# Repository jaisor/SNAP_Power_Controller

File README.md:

# SNAP Power Controller

A small solar charger board for a single-cell (1S) Li-ion/LiPo battery, built for solar-powered LoRa mesh nodes such as [SNAP v1.2](https://makerworld.com/en/models/3360988-snap-v1-2-solar-node-adaptable-platform-2x200ma). Up to four 5V panels feed a CN3163 linear charger through a 5V input limiter. A switched output powers the node, and an INA3221 reports the battery's and the panels' voltage and current over I2C.

Designed in KiCad 10.

> **Branch `cn3163`:** this is a variant of the board on `main`. A CN3163 linear solar charger replaces `main`'s CN3791 buck charger. The board is the same size as `main`'s, with the same connectors in the same places.
>
> What changes in the circuit:
>
> - **Removed:** the switching stage and its support parts: Q1, D2, L1, the sense resistor R5, the MPPT divider R3/R4, C2, C4, C5 and the old R2. Ten parts go, one comes back (the new R2).
> - **Added:** R2 = 1.5k, which sets the charge current to 0.79A (1188V / R2). Also U3, an LDL1117S50R 5V regulator with its output capacitor C2, as an input voltage limiter.
> - **Kept:** the four diode-isolated solar inputs, the INA3221 and its two shunts, both switch headers, the reverse-battery FET, the status LEDs behind JP1, and every connector and pinout.
> - **Panel voltage:** every CN3163 pin has a 6.5V absolute maximum, and a panel floats to its open-circuit voltage once the battery is full. U3 sits between the panels and the charger and holds the charger's supply at 5.0V, so panels up to 18V open-circuit are safe. While charging, the CN3163 pulls the panels down to about 4.5V and U3 is simply fully on, costing about 0.3Ω: roughly 70mV at 0.25A and 0.25V at 0.8A. The board is still meant for 5–6V panels; anything higher only makes heat.
> - **Solar tracking is built in and fixed.** The CN3163 cuts the charge current to keep its input at 4.4V or above, so there is no set point to tune.
> - **It is a linear charger.** The difference between input and battery voltage is lost as heat in the chip, about 0.55W at 0.79A from panels, and up to about 1W when the supply holds 5V. It reduces the current by itself to stay near 130°C.

> **Status:** the schematic is complete and passes ERC. The PCB (36.4 × 23.6 mm, 1mm corner chamfers, four M2 mounting holes, two layers) is **placed and routed**, with no DRC errors and no schematic parity issues. It hasn't been built, and it hasn't had a manual layout review. The test results under [Testing](#testing) are from v1.0 boards with the CN3791 and an INA219.

## Built for solar mesh nodes

This controller is meant for solar mesh nodes like the [SNAP v1.2: Solar Node Adaptable Platform](https://makerworld.com/en/models/3360988-snap-v1-2-solar-node-adaptable-platform-2x200ma). It simplifies their build in three ways:

- **Easy, clean connections:** the panels, battery, node and switches each plug into their own connector.
- **Solar charging for 5V panels:** a charger that holds its input at 4.4V or above, so a weak panel isn't dragged down, with a diode for every panel built into the board.
- **I2C power sensing:** the battery and the total solar input, read at the same time.

I2C power sensors are supported natively by both [Meshtastic](https://meshtastic.org) and [MeshCore](https://github.com/meshcore-dev/MeshCore). In most cases the node recognizes the INA3221 automatically once it's connected.

In the SNAP v1.2 example build, shown below, the board replaces several separately wired parts:

| Example build part | With this board |
|---|---|
| CN3158 MPPT module (SDBK03TA) | CN3163 linear solar charger, holding its input at 4.4V or above and charging at 0.79A, behind a 5V input limiter |
| One 1N5819 per panel, soldered inline | A 1N5819W per input on the board, for up to four panels |
| Hand-soldered panel, battery and node wiring | Plug-in connectors for every connection: Micro JST 1.25, with 2.54mm pin headers for the switches |
| Latching on/off switch wired into the battery lead | Two switch connectors: SW_BATT cuts the battery, SW_LOAD cuts only the node |
| (none) | INA3221 power monitor on I2C, reading the battery and the total solar input at once |

### Example wiring

| Board connector | Connects to |
|---|---|
| J1, J2 (Solar_5V) | Two [FellDen 5V 200mA 110×60mm panels](https://www.amazon.com/dp/B0BND5NYGK), the ones SNAP v1.2 uses. J3 and J4 take up to two more |
| J5 (BATT) | An 18650 Li-ion cell (1S, 3.0–4.2V) in its holder |
| J8 (SW_LOAD) | The SNAP on/off switch cap's latching button. To cut the battery entirely, use J7 (SW_BATT) as well, or instead |
| J7 / J8 left unswitched | Both switch connectors are in series with the power path, so an unused one needs a 2.54mm jumper cap, or a wire bridging its pads on the back of the board. Otherwise the battery or the node stays disconnected |
| J6 (VOUT) | The XIAO nRF52840's BAT+ / BAT− pads, which is where SNAP powers it from the 18650 today |
| J9 (I2C) | XIAO 3V3 → VCC, D6 → SDA, D7 → SCL, GND → GND, on a 4-wire cable coloured red VCC, black GND, yellow SCL, white SDA. These pins need a Meshtastic build with I2C on D6/D7 (see the table below) |
| JP1 (LED) | Nothing. JP1 is bridged by a trace as supplied, so the status LEDs work. To turn them off for good, cut the trace between its pads |
| JP2 (NTC) | Nothing, or a 10k B3950 NTC taped to the cell. JP2 is bridged as supplied, which turns temperature sensing off. To use the NTC, cut the trace between JP2's pads and solder the NTC's wires to them |

The INA3221 reads the battery's charge and discharge current and what the panels deliver in total, both at the same time. There's no switch to set.

The XIAO's I2C pins depend on the firmware build. D4 and D5 can't be used with the Wio-SX1262, because the radio uses them.

| Firmware build | SDA | SCL | Status |
|---|---|---|---|
| Meshtastic `seeed_xiao_nrf52840_kit`, custom build with I2C on D6/D7 | D6 | D7 | Tested on a v1.0 board |
| Meshtastic `seeed_xiao_nrf52840_kit_i2c` | D6 | D7 | From the firmware source, not tested |
| Meshtastic `seeed_xiao_nrf52840_kit`, unmodified (D6/D7 are reserved for the GNSS module) | NFC1 pad (underside) | NFC2 pad (underside) | From the firmware source, not tested |
| MeshCore `Xiao_nrf52` | D7 | D6 | From the firmware source, not tested |

The INA3221 uses address 0x42. Meshtastic also expects the DFRobot Lark weather sensor at 0x42, so the two can't share a bus.

In Meshtastic, enable power metrics in the telemetry settings so the readings are sent to the mesh.

## Features

- **Solar input:** up to four 5V panels in parallel (Micro JST 1.25), each isolated by its own 1N5819W Schottky (SOD-123), good for 0.5A per input, so a shaded or unplugged panel doesn't drag the others down.
- **Input limiter:** U3, an LDL1117S50R 5.0V regulator (ST), keeps the charger's supply at or below 5V, so panels up to 18V open-circuit can't damage the 6.5V-rated charger. While charging it is fully on and only adds its on-resistance.
- **Charging:** [CN3163](https://kaspars.net/wp-content/uploads/2023/12/CN3163.pdf) linear charger for one cell. Charges at 0.79A to 4.2V (1%), CC/CV, with a 10% precharge for deeply discharged cells, termination at 10% of the charge current and automatic recharge. An on-chip loop reduces the charge current to keep its input at 4.4V or above, and thermal regulation reduces it to keep the chip near 130°C.
- **Battery and load switching:** connectors for two panel-mount switches. **SW_BATT** disconnects the battery from everything. **SW_LOAD** cuts only the output, so the battery keeps charging.
- **Output:** VOUT connector (Micro JST 1.25) that powers the module from the battery.
- **Reverse-battery protection:** Q2, a P-channel MOSFET between the battery connector and the rest of the board. A cell plugged in backwards is blocked instead of shorting through the charger. With the cell the right way round, Q2 is fully on in both directions, adding about 60mV of drop at 0.8A.
- **Power monitoring:** [INA3221](https://www.ti.com/lit/ds/symlink/ina3221.pdf) at I2C address 0x42, on two channels: the battery (bidirectional current plus voltage) and the total solar input. The third channel is unused.
- **Battery temperature (optional):** with a 10k B3950 NTC against the cell, wired to JP2's pads, the CN3163 pauses charging below about 1°C and above about 46°C. JP2 is bridged by a thin trace as supplied, which turns sensing off; cut the trace to use the NTC.
- **Status LEDs:** red while charging, green when charging is done. They're powered through JP1, marked `LED` on the top of the board: two pads joined by a trace, the same as JP2. As supplied the LEDs work, and a lit LED draws about 3mA from the panels (never from the cell). Cut the trace to disconnect them; a solder blob across the pads turns them back on.

## Choosing panels

While charging, the CN3163 holds its input at 4.4V or above. Each input diode drops about 0.35V and U3 another 0.07–0.25V, so a panel has to deliver its power at about 4.8–5.0V. A panel's maximum-power voltage falls about 0.4% per °C, so what matters is how the panel does hot, not at its rated 25°C.

- **"6V" panels** (12 cells, about 7.2V open-circuit) are preferred. They stay above that voltage in heat.
- **"5V" panels** (10 cells, about 6.0V open-circuit) lose part of their output on hot days, when their maximum-power voltage falls to about 4.2V.
- **"5V" panels that only reach about 5.5V open-circuit** lose most of their output in heat.

There is no setting to change for a different panel: the CN3163's 4.4V input threshold is fixed. `main`'s README models the CN3791 board, whose set point is about the same, for the two kinds of 5V panel; expect a little less here, because of U3's drop.

## Schematic

The schematic follows the CN3163 datasheet's typical application circuit (Figure 1), with these changes:

| Item | Value | Why |
|---|---|---|
| Charge current | 0.79A (R2 = 1.5k) | I<sub>CH</sub> = 1188V / R2. Leaves margin on the 1.0A-rated connectors; use 2.4k for 0.5A with small cells. |
| Input limiter U3 | LDL1117S50R, 5.0V, SOT-223 | Every CN3163 pin is rated 6.5V at most, and an unloaded panel sits at its open-circuit voltage. A shunt clamp would have to sink about half of each panel's short-circuit current to hold it down, and an overvoltage cut-off would switch off in bright sun, so a series regulator was used. U3 is rated for 18V in (20V absolute maximum). Its output capacitor C2 is 10µF. |
| Status LED supply | From U3's output | The LEDs' resistor R1 and JP1 take their supply after U3, because CHRG and DONE are 6.5V pins too. |
| Battery capacitor C3 | 10µF | The datasheet asks for 1µF to 22µF on BAT. |
| Temperature divider | R3 = 4.7k (VCHG to TEMP), R4 = 47k (TEMP to GND), NTC across R4 | The datasheet's Figure 7. Charging runs while TEMP is between 45% and 80% of the CN3163's supply, so the window doesn't depend on the panel voltage. Sized for a 10k B3950 NTC and 0–45°C, the exact values are 4.86k and 46.1k; 4.7k and 47k give about 1–46°C. |
| Temperature jumper JP2 | Bridged by a trace; its pads are the NTC's pads | Without an NTC, TEMP would sit at 91% and charging would never start. Bridged, JP2 holds TEMP at GND, which turns sensing off, as the datasheet allows. R3 then draws about 1mA from the 5V supply while the panels are lit. Cut the trace before fitting the NTC. |
| Blocking diode | none | The input diodes stop the battery feeding back into the panels. In the dark the CN3163 sleeps and draws under 3µA from the battery (datasheet figure, not measured on a board). |
| Input diodes | 1N5819W, SOD-123 (40V/1A) | Rated 0.5A per input here: about 0.2W in the diode, which the SOD-123 package handles with margin in a warm enclosure. |

## PCB

| Area | Parts |
|---|---|
| Corners | M2 mounting holes H1–H4 |
| Top edge | Solar inputs J1 (`+S1-`) and J2 (`+S2-`), the 4-pin I2C connector J9, then the INA3221 (U2) with its bypass capacitor C6 |
| Upper middle | Input diodes D5/D6, the solar shunt R7 and the input capacitor C1, with the I2C pull-ups R8/R9 above the charger and its current-setting resistor R2 beside them. On the right: the reverse-battery MOSFET Q2 and the battery shunt R6 |
| Middle | CN3163 (U1), with the 5V limiter U3 below and to its left. The limiter's output capacitor C2 is under U1, and the battery capacitor C3 to its right. The status LEDs D3/D4 and R1 sit beside the LED solder jumper JP1 at the left edge |
| Left edge, top | The NTC pads JP2 (`NTC`) left of D5, with the temperature divider R3/R4 below them |
| Right edge | Battery (J5, `+1S BATT-`) and VOUT (J6, `+LOAD-`) |
| Bottom edge | Solar inputs J4 (`+S4-`) and J3 (`+S3-`), directly under J1 and J2, with their diodes D8/D7, then the switch headers J7 (`SW BATT`) and J8 (`SW LOAD`) |

The connectors, the INA3221, the input diodes, the shunts, Q2 and the LEDs are in exactly the same places as on `main`'s board (JP1 sits 3.2mm lower and R1 lies flat under D3, to make room for R3/R4); only the charger parts in the middle differ. Reference designators aren't printed; the silkscreen carries only function labels. The holes are plain non-plated 2.2mm M2 holes, 2.5mm in from each edge. Mount the board with nylon washers and standoffs; see [Dimensions](#dimensions).

The CN3163's 3D model doesn't show in the renders (the footprint's model file seems to be missing from KiCad's library); only its pads appear.

### Dimensions

The [wiring diagram](#built-for-solar-mesh-nodes) includes a dimension drawing to scale.

| | |
|---|---|
| Outline | 36.4 × 23.6mm, with a 1mm × 45° chamfer on each corner |
| Thickness | 1.6mm PCB, two layers. All parts are on the top side; the through-hole connector pins stick out the back |
| Mounting holes | Four, 2.2mm diameter, not plated, for M2 screws |
| Mounting hardware | M2 screws with heads no wider than 4mm, and nylon washers and standoffs. **Don't use metal washers or metal standoffs:** a 5mm M2 washer reaches within 0.3mm of C6's bare pad at H2, and tracks pass about 3mm from the hole centres |
| Hole positions | One in each corner, centre 2.5mm from both edges |
| Hole spacing | 31.4mm across, 18.6mm down, centre to centre |

**Silkscreen labels:**

- **Connector labels with polarity:** each solar, battery and VOUT connector has one label centred under or over it, with `+` on the pin-1 side and `-` on the GND side: `+S1-` to `+S4-` on J1–J4, `+1S BATT-` on J5 and `+LOAD-` on J6.
- **Switch headers:** `SW BATT` (J7) and `SW LOAD` (J8) are vertical labels left of the headers.
- **I2C connector:** `I2C` under J9 on the front. The pin names (`VCC`, `GND`, `SCL`, `SDA`) are printed under its pads on the back.
- **LED jumper:** `LED` beside JP1.
- **NTC pads:** `NTC` above JP2.
- **Back:** the module ID, "SNAP Power Controller CN3163 v1.0 / Nov. 20, 2026". Under it, a reminder to check polarity, the limits listed under [Safety](#safety), and a short no-warranty notice.
- **Text size:** the front labels are 0.6mm text, the board's minimum. Board houses often recommend 0.8–1mm or more, so check that yours prints 0.6mm cleanly. The back label is 0.8 to 1.0mm.

**Routing** (a grid auto-router adapted from `tools/route-pcb.py`, with the tightest connections placed by hand first; the board file is the source of truth):

- **Ground:** both layers have a GND pour, and the bottom one is cut only by short hops. Most surface-mount GND pads have their own via to it. Six vias in the CN3163's exposed pad carry its heat to the bottom plane, and no track runs on the bottom layer under the chip.
- **Power path:** R7 → C1 → U3 → U1 → C3 → J7 runs on short tracks on the top layer.
- **Track widths:** power paths are 0.6mm, 0.4mm where 0.6mm doesn't fit. Signals are 0.25mm, with 0.2mm on the INA3221's escape tracks.
- **Kelvin sensing:** the INA3221's channel inputs connect straight to the pads of their shunt resistors (R6, R7).
- **Temperature line:** TEMP runs on the bottom layer from U1 pin 1 to the NTC pads, under the input diodes, so it is the one long track that cuts the bottom ground plane.
- **Layer use:** about 277mm of track on the top layer and 84mm on the bottom.
- **Size:** 199 track segments and 44 vias, 17 of them on GND. VCHG reaches the NTC divider (R3) on the bottom layer, under JP1.
- **Mounting holes:** no copper except ground comes within 3mm of a hole centre, apart from two bare pads: C6's at H2 (2.8mm) and JP1's at H3 (2.7mm, fed through R1, 1k). That's why the hardware must be nylon.
- **Checks:** DRC reports 0 violations and 0 unconnected items, and schematic parity is clean.

Review it before ordering, especially the charger's heat path (the exposed pad, its vias and the ground plane).

Still to do: a manual layout review before ordering (see Fabrication).

## Connectors

| Ref | Connector | Pin 1 | Pin 2 | Notes |
|---|---|---|---|---|
| J1–J4 | Micro JST 1.25, 2-pin | Panel + | GND | 5V solar panels, any combination of 1–4 |
| J5 | Micro JST 1.25, 2-pin | Battery + | GND | 1S Li-ion/LiPo, 4.2V |
| J6 | Micro JST 1.25, 2-pin | VOUT | GND | Battery voltage out to the powered module, through SW_LOAD |
| J7 | 2.54mm pin header, 2-pin | VBAT (charger) | BATT+ (battery) | SW_BATT: panel-mount SPST switch, rated ≥1A or the module's peak current |
| J8 | 2.54mm pin header, 2-pin | VBAT | VOUT | SW_LOAD: panel-mount SPST switch, same rating |
| J9 | Micro JST 1.25, 4-pin | VCC (3.3–5V) | GND | Pin 3 = SCL, pin 4 = SDA, matching the common red/black/yellow/white 4-wire cable. VCC comes from the MCU and powers the INA3221. v1.0 boards have SDA on pin 2 and GND on pin 4. |

J1–J6 and J9 are Micro JST 1.25 (Molex PicoBlade-compatible) vertical headers, Molex 53047-0210 (2-pin) and 53047-0410 (4-pin). They mate with standard female cable housings (Molex 51021). J7 and J8 are standard 2.54mm vertical pin headers, which take a 2.54mm female housing or a jumper cap. Notes:

- **Current:** PicoBlade contacts are rated 1.0A. The charge current is set to 0.79A to stay under that on the battery connector (J5). Keep the module's load current under 1A too, since it flows through J5 when the panels are dark.
- **No keying between functions:** J1–J6 are the same 2-pin type, so a battery lead fits a solar socket. Check the silkscreen before plugging in. The switch headers take a different plug, so they can't be mixed up with these.
- **Battery polarity:** "JST 1.25" LiPo pigtails have no standard polarity. Check that red goes to the pin marked `+` (pin 1 on J5) before connecting. Q2 blocks a reversed cell, but fit the cell with SW_BATT off anyway: with SW_BATT on in sunlight, the charger's output can partly turn Q2 on and push a limited current into a reversed cell, which heats Q2.
- **NTC:** JP2 is not a connector: its two pads take the NTC's wires directly. Either way round works. Keep the NTC on the cell, away from the board: the CN3163 itself runs hot.
- **Reading the marks:** each of J1–J6 has a `+name-` label: pin 1 (`+`) is on the `+` side and GND on the `-` side. All six face the same way, so pin 1 is the left pin with the board read as printed.

**Operating note:** if SW_BATT is off while the panels are in sun, the charger has no battery to charge, and its output isn't meant to power the node in that state. Keep SW_LOAD off then.

## Power monitor (INA3221)

- **Address:** 0x42 (A0 = SDA). That's the INA3221 default in both Meshtastic and MeshCore.
- **Shunts:** both are 0.1Ω, which both firmwares assume. Full scale is ±163.8mV, so about ±1.64A, in 0.4mA steps.
- **What it can't measure:** sleep current. A sleeping node draws 50–100µA, which is 5–10µV across 0.1Ω, below the chip's 40µV step and its offset (up to 80µV). The monitor is for charge and load telemetry, in the tens to hundreds of milliamps; profile sleep current on the bench with a tool made for it. A larger battery shunt isn't an option here: 0.5–1Ω would drop 0.4–0.8V at the 0.79A charge current and exceed the chip's input range.
- **Pull-ups:** R8/R9 are 10k I2C pull-ups to the MCU's VCC. Leave them off if the MCU board already has pull-ups.

| Channel | Shunt | Current | Bus voltage |
|---|---|---|---|
| 1 | R6, between BATT+ and the cell | Positive while charging, negative while discharging | Cell voltage, readable even with SW_BATT off. It's measured after Q2, so it reads up to about 50mV off while current flows |
| 2 | R7, between the PV bus and VIN | Total solar current, always ≥ 0 | VIN (panel voltage minus the diode drop), before the 5V limiter |
| 3 | None: both inputs are tied to GND | Unused, reads zero | Unused, reads zero |

**Firmware support** (checked in the source code on 2026-11-09, not yet on hardware):
- **Meshtastic:** looks for an INA3221 at 0x42. It reports all three channels' voltage and current as power metrics (channel 3 reads about zero on this board), and uses channel 1 as the battery by default.
- **MeshCore:** the XIAO nRF52 build includes INA3221 support (`ENV_INCLUDE_INA3221`). It reports voltage, current and power for each channel.

## Testing

The CN3163 board hasn't been built. These tests are from v1.0 boards, which have the CN3791 charger and an INA219:

| Test | Setup | Status |
|---|---|---|
| First power-up | Board wired to a XIAO + Wio-SX1262, running Meshtastic built from `seeed_xiao_nrf52840_kit` with I2C on D6/D7 | Done. Everything seems to work as expected, including the INA219 over I2C |
| INA219 battery current | Same setup, battery at about 4V | Done. Discharging: about −12 to −15mA. Charging from the XIAO's USB: +100mA |
| Sunlight | Board wired into a real solar node with 4 × 60mA panels, with metrics tracked in Grafana dashboards | In progress. Voltage and charge current rose as expected when exposed to sunlight. One reading in the Meshtastic app: 4.56V, 110.5mA |

The signs match the expected convention: positive while charging, negative while discharging. The USB reading comes from the XIAO's own charger, so it doesn't test the board's charger. The sunlight reading is from SW3's SOLAR position: 4.56V is above a Li-ion cell's 4.2V and close to the 4.58V MPPT set point of the board tested. It's a single reading, and longer-term results are still to come. These tests used a board with Micro JST 1.25 connectors on J7 and J8, so the pin-header version hasn't been built yet. In the sunlight test build, J7 and J8 are bridged with wire on the back of the board, so neither switch is fitted.

## Safety

This is an experimental design for charging a lithium-ion cell. It's provided as is, with no warranty, and hasn't been certified to any safety standard. If you build it, you're responsible for:

- Assembling it correctly and checking connector polarity before connecting a cell. J1–J6 share one connector type, so a lead plugs into the wrong socket easily. Q2 protects against a reversed cell on J5, but not against every fault, such as a battery plugged into a solar input.
- Using a protected cell or a separate protection circuit. The CN3163 charges the cell but doesn't protect it from over-discharge or short circuits.
- Deciding on temperature sensing. As supplied, JP2 turns it off, and the board will charge a frozen or hot cell. Li-ion cells shouldn't be charged below 0°C; fit the NTC if the node sees frost or strong sun.
- Allowing for heat. The CN3163 is a linear charger and turns up to about 1W into heat at full current; it limits itself near 130°C, but the board and the enclosure around it get warm.
- Fusing, wiring and an enclosure suited to where the node is installed, including outdoor heat and moisture.
- Mounting it with nylon washers and standoffs. Metal hardware can reach copper near the holes, including the unfused battery rail.
- Not using it where a failure could hurt someone or damage property.

**Limits**, also printed on the back of the board:

| | Limit | Set by |
|---|---|---|
| Battery | One Li-ion or LiPo cell (1S), charged to 4.2V | The CN3163's fixed charge voltage |
| Panel voltage | 18V open-circuit at most. The board is meant for 5–6V panels; a higher-voltage panel is safe but its extra voltage is only lost as heat | The input rating of U3, the 5V limiter in front of the charger |
| Panel current | 0.5A per input | Heat in each input's 1N5819W diode |
| Load on VOUT | 1A | The connector contacts at J5 and J6 |

**No warranty:** the board is provided as is, and you use it at your own risk. Where the law allows a limit, liability for a board you bought is limited to the price you paid for it. The design itself is covered by the disclaimer in the [licence](#license).

## Fabrication

This board's release is [v1.0_cn3163](https://github.com/jaisor/SNAP_Power_Controller/releases/tag/v1.0_cn3163) (Nov. 20, 2026), with the files below attached. The repository's latest release, v1.1, is `main`'s CN3791 board, and its files don't match this one. The commands below regenerate the package into `output/fab/`, which isn't tracked in git:

| File | Contents |
|---|---|
| `SNAP_Power_Controller_CN3163_v1.0_gerbers.zip` | Upload this to the board house. 9 Gerber X2 layers (copper, mask, paste and silkscreen on both sides, plus the outline), a Gerber job file, plated and non-plated Excellon drill files, and drill maps |
| `FAB_NOTES.txt` | Order settings: 2 layers, FR-4 1.6mm, 1oz copper, 36.4 × 23.6mm, 0.2mm/0.2mm minimum track/space, 0.3mm minimum drill, tented vias, four 2.2mm non-plated holes. Also assembly cautions |
| `SNAP_Power_Controller_CN3163_v1.0_BOM.csv` | BOM in JLCPCB format (Comment, Designator, Footprint, LCSC Part #), plus a Manufacturer Part column for the specific parts |
| `SNAP_Power_Controller_CN3163_v1.0_CPL.csv` | Pick-and-place file for top-side assembly, in the same coordinates as the Gerbers |

Every BOM line has a JLCPCB/LCSC part number, checked on jlcpcb.com on Nov. 20, 2026. They are Basic parts except D3, the connectors, U1, U2 and U3. Re-check stock before ordering, and check rotation and polarity in the assembler's preview. D5–D8 are Changjiang B5819W (C8598), rated 1A with 0.6V at most at 1A. The PicoBlade headers and the J7 and J8 pin headers are through-hole parts. JP1 is a solder jumper made of bare pads, so it has no part to place.

Regenerating the package (after the board is final and DRC is clean):

```bash
OUT=output/fab
P=SNAP_Power_Controller
kicad-cli pcb export gerbers --layers F.Cu,B.Cu,F.Paste,B.Paste,F.Silkscreen,B.Silkscreen,F.Mask,B.Mask,Edge.Cuts --subtract-soldermask --check-zones -o $OUT/gerbers $P.kicad_pcb
kicad-cli pcb export drill --format excellon --excellon-units mm --excellon-zeros-format decimal --drill-origin absolute --excellon-separate-th --generate-map --map-format gerberx2 -o $OUT/gerbers/ $P.kicad_pcb
kicad-cli pcb export pos --format csv --units mm --side both -o $OUT/pos-kicad.csv $P.kicad_pcb
kicad-cli sch export bom --fields 'Value,Reference,Footprint,${QUANTITY}' --labels 'Comment,Designator,Footprint,Qty' --group-by 'Value,Footprint' --ref-range-delimiter '' --exclude-dnp -o $OUT/bom-kicad.csv $P.kicad_sch
node tools/fab-package.js $OUT
```

## Repository layout

```
SNAP_Power_Controller.kicad_pro / .kicad_sch / .kicad_pcb   KiCad project
SolarNode.kicad_sym             project symbol library (CN3163)
SolarNode.pretty/               project footprint library (JP2's bridged NTC pads)
sym-lib-table / fp-lib-table
tools/
  gen-schematic.js              generates the schematic (Node)
  place-pcb.py                  places the earlier 52 × 29mm CN3163 board: footprints, labels, holes, outline (KiCad Python / pcbnew)
  draw-routes.py                draws the earlier 52 × 29mm board's tracks, vias and GND pours (run after place-pcb.py)
  route-pcb.py                  the earlier auto-router, kept for reference (v1.0's copper came from it)
  make-diagram.py               draws docs/images/wiring-diagram.png from the board render
  fab-package.js                JLCPCB-style BOM/CPL, fab notes and Gerber zip from the kicad-cli exports
docs/images/                    images used in this README (snap/: photos from the SNAP v1.2 MakerWorld post)
CLAUDE.md                       design decisions and working notes
LICENSE                         CERN-OHL-P-2.0 (hardware design and documentation)
tools/LICENSE                   MIT (scripts)
```

The schematic is generated by `tools/gen-schematic.js`. The board was built from it and routed with a router that isn't in the repo, so the board file is the source of truth for the layout; the board scripts in `tools/` build the earlier 52 × 29mm layout. Both are checked with `kicad-cli` ERC/DRC (including schematic parity). See [CLAUDE.md](CLAUDE.md) for the full design rationale and workflow. Generated outputs (`output/`: BOM, reports, fab files) are not tracked.

## Regenerating the design

The schematic can be rebuilt from its script. Run these from the repo root, with `kicad-cli` from KiCad 10:

```bash
# Schematic (Node): rewrites the .kicad_sch, SolarNode.kicad_sym and sym-lib-table
node tools/gen-schematic.js
kicad-cli sch erc --format json --severity-all -o erc.json SNAP_Power_Controller.kicad_sch
# Board check: expect 0 violations, 0 unconnected, 0 parity issues
kicad-cli pcb drc --schematic-parity --severity-all --format json -o drc.json SNAP_Power_Controller.kicad_pcb
```

**Don't run `tools/place-pcb.py` or `tools/draw-routes.py` on this design.** They rebuild the earlier 52 × 29mm board and overwrite the board file. The scripts overwrite their output files. Once you edit the schematic in KiCad, stop regenerating it (or port your edits into the script first).

Refreshing the images in `docs/images/`:

```bash
kicad-cli sch export svg -o docs/images SNAP_Power_Controller.kicad_sch
kicad-cli pcb render --side top --width 1600 --height 900 --quality high --zoom 1.35 -o docs/images/pcb-top.png SNAP_Power_Controller.kicad_pcb
kicad-cli pcb render --side bottom --width 1600 --height 900 --quality high --zoom 1.35 -o docs/images/pcb-bottom.png SNAP_Power_Controller.kicad_pcb
kicad-cli pcb render --width 1600 --height 1000 --quality high --perspective --rotate "-40,0,-25" -o docs/images/pcb-iso.png SNAP_Power_Controller.kicad_pcb
```

(The schematic export is named `SNAP_Power_Controller.svg`; rename it to `schematic.svg`.)

After refreshing `pcb-top.png`, redraw the wiring diagram with KiCad's Python, which includes Pillow and NumPy:

```bash
"C:/Program Files/KiCad/10.0/bin/python.exe" tools/make-diagram.py
```

## License

Copyright 2026 Jordan Marinov (JaisorGadgets).

The hardware design (schematic, board, symbol library) and its documentation, including the images in `docs/images/`, are licensed under the [CERN Open Hardware Licence Version 2 – Permissive](LICENSE) (CERN-OHL-P-2.0). You may redistribute and modify them, and make and sell products from them, under the terms of the licence. They are distributed WITHOUT ANY EXPRESS OR IMPLIED WARRANTY, INCLUDING OF MERCHANTABILITY, SATISFACTORY QUALITY AND FITNESS FOR A PARTICULAR PURPOSE. See section 5 of the licence for the disclaimer and limitation of liability.

The scripts in `tools/` are licensed under the [MIT License](tools/LICENSE).

Source location: https://github.com/jaisor/SNAP_Power_Controller

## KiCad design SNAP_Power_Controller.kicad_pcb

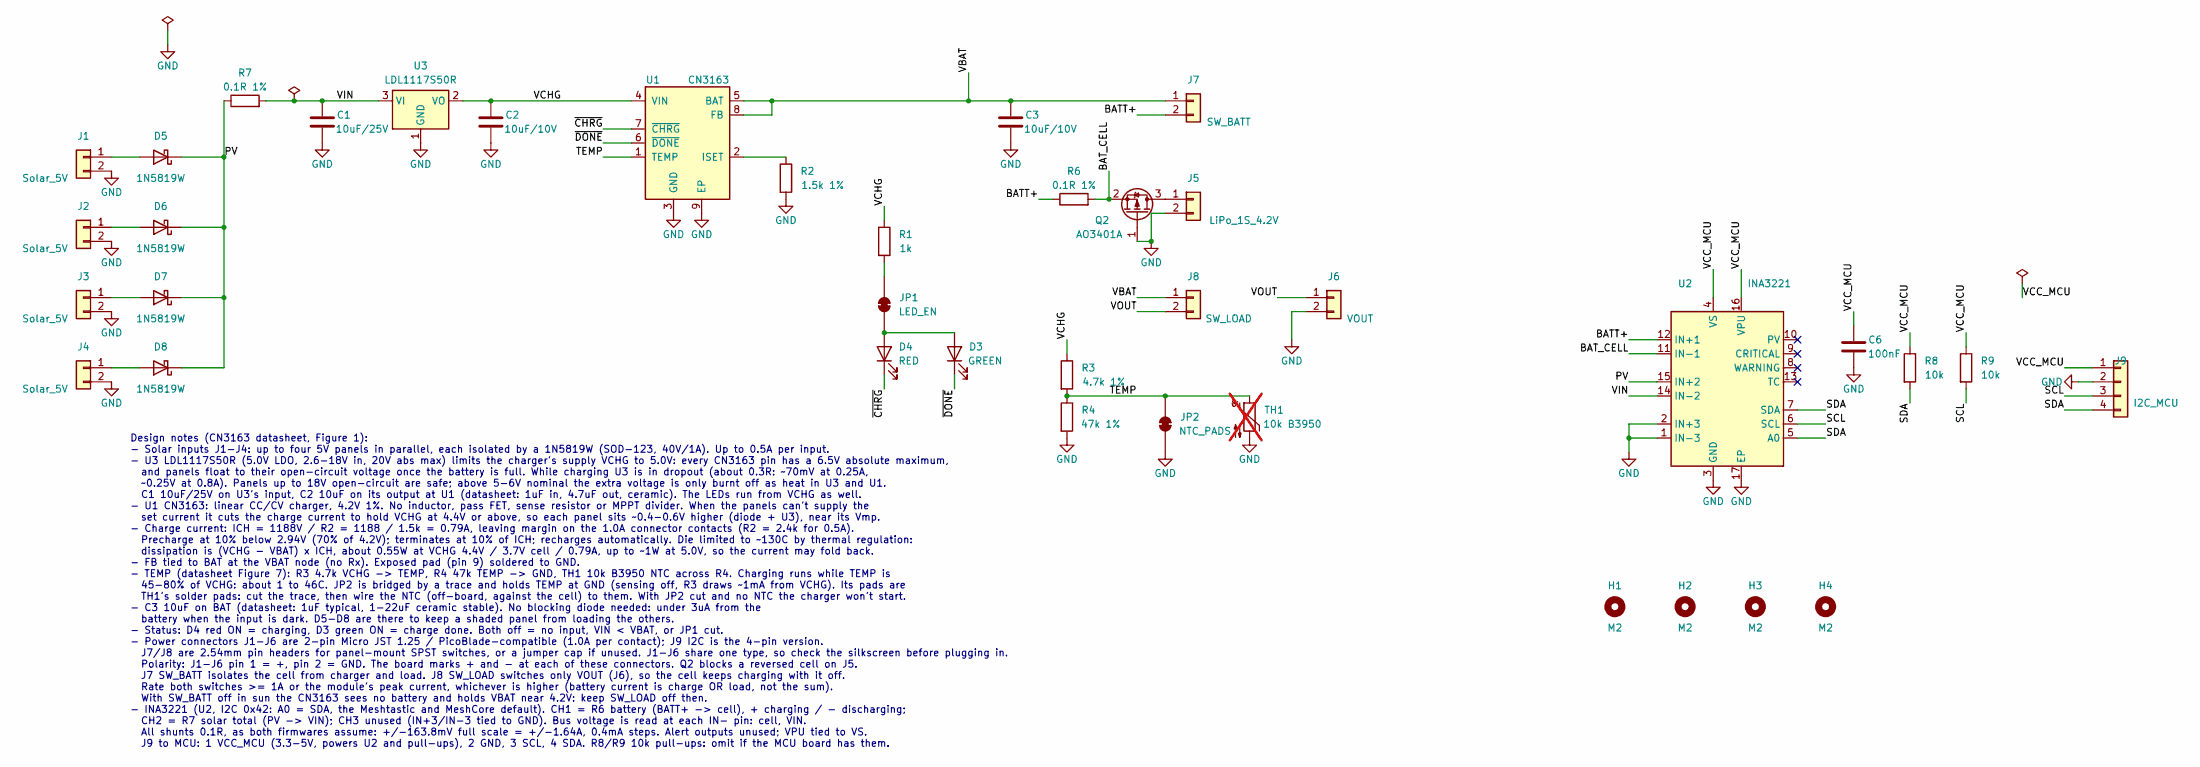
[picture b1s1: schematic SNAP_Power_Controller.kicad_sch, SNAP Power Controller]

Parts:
C1: 10uF/25V; C_1206_3216Metric
C2, C3: 10uF/10V; C_1206_3216Metric
C6: 100nF; C_0603_1608Metric
D3: GREEN; LED_0603_1608Metric
D4: RED; LED_0603_1608Metric
D5, D6, D7, D8: 1N5819W; D_SOD-123
H1, H2, H3, H4: M2; MountingHole_2.2mm_M2
J1, J2, J3, J4: Solar_5V; Molex_PicoBlade_53047-0210_1x02_P1.25mm_Vertical
J5: LiPo_1S_4.2V; Molex_PicoBlade_53047-0210_1x02_P1.25mm_Vertical
J6: VOUT; Molex_PicoBlade_53047-0210_1x02_P1.25mm_Vertical
J7: SW_BATT; PinHeader_1x02_P2.54mm_Vertical
J8: SW_LOAD; PinHeader_1x02_P2.54mm_Vertical
J9: I2C_MCU; Molex_PicoBlade_53047-0410_1x04_P1.25mm_Vertical
JP1: LED_EN; NTC_SolderPads_Bridged_P2.54mm
JP2: NTC_PADS; NTC_SolderPads_Bridged_P2.54mm
Q2: AO3401A; SOT-23
R1: 1k; R_0603_1608Metric
R2: 1.5k 1%; R_0603_1608Metric
R3: 4.7k 1%; R_0603_1608Metric
R4: 47k 1%; R_0603_1608Metric
R6, R7: 0.1R 1%; R_1206_3216Metric
R8, R9: 10k; R_0603_1608Metric
TH1: 10k B3950; not fitted
U1: CN3163; SOIC-8-1EP_3.9x4.9mm_P1.27mm_EP2.41x3.3mm
U2: INA3221; Texas_RGV0016A_VQFN-16-1EP_4x4mm_P0.65mm_EP2.1x2.1mm
U3: LDL1117S50R; SOT-223-3_TabPin2

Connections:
/BATT+: J7.2, R6.1, U2.12 (IN+1)
/BAT_CELL: Q2.2 (S), R6.2, U2.11 (IN-1)
/PV: D5.1 (K), D6.1 (K), D7.1 (K), D8.1 (K), R7.1, U2.15 (IN+2)
/SCL: J9.3, R9.2, U2.6 (SCL)
/SDA: J9.4, R8.2, U2.5 (A0), U2.7 (SDA)
/TEMP: JP2.1 (A), R3.2, R4.1, TH1.1, U1.1 (TEMP)
/VBAT: C3.1, J7.1, J8.1, U1.5 (BAT), U1.8 (FB)
/VCC_MCU: C6.1, J9.1, R8.1, R9.1, U2.4 (VS), U2.16 (VPU)
/VCHG: C2.1, R1.1, R3.1, U1.4 (VIN), U3.2 (VO)
/VIN: C1.1, R7.2, U2.14 (IN-2), U3.3 (VI)
/VOUT: J6.1, J8.2
/~CHRG: D4.1 (K), U1.7 (~CHRG)
/~DONE: D3.1 (K), U1.6 (~DONE)
GND: C1.2, C2.2, C3.2, C6.2, J1.2, J2.2, J3.2, J4.2, J5.2, J6.2, J9.2, JP2.2 (B), Q2.1 (G), R2.2, R4.2, TH1.2, U1.3 (GND), U1.9 (EP), U2.1 (IN-3), U2.2 (IN+3), U2.3 (GND), U2.17 (EP), U3.1 (GND)
unnamed: D3.2 (A), D4.2 (A), JP1.1 (A)
unnamed: D5.2 (A), J1.1
unnamed: D6.2 (A), J2.1
unnamed: D7.2 (A), J3.1
unnamed: D8.2 (A), J4.1
unnamed: J5.1, Q2.3 (D)
unnamed: JP1.2 (B), R1.2
unnamed: R2.1, U1.2 (ISET)

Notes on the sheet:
Design notes (CN3163 datasheet, Figure 1): - Solar inputs J1-J4: up to four 5V panels in parallel, each isolated by a 1N5819W (SOD-123, 40V/1A). Up to 0.5A per input. - U3 LDL1117S50R (5.0V LDO, 2.6-18V in, 20V abs max) limits the charger's supply VCHG to 5.0V: every CN3163 pin has a 6.5V absolute 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

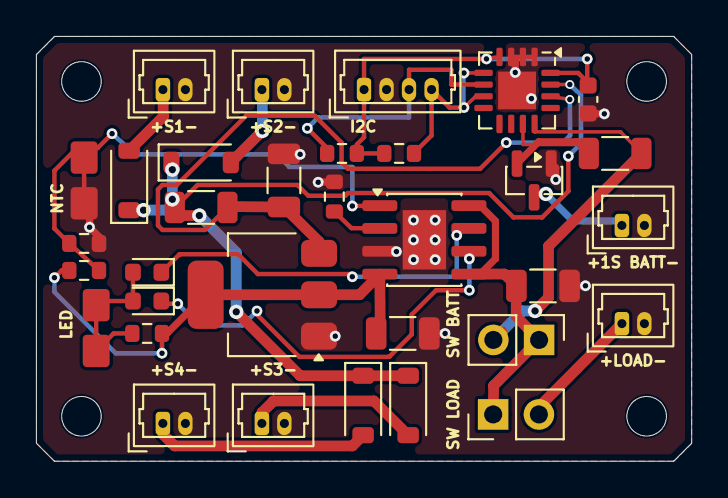
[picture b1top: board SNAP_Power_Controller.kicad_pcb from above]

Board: 2 copper layers, 36.4 x 23.6 mm, 37 parts (0 on the bottom side), 22 nets.
